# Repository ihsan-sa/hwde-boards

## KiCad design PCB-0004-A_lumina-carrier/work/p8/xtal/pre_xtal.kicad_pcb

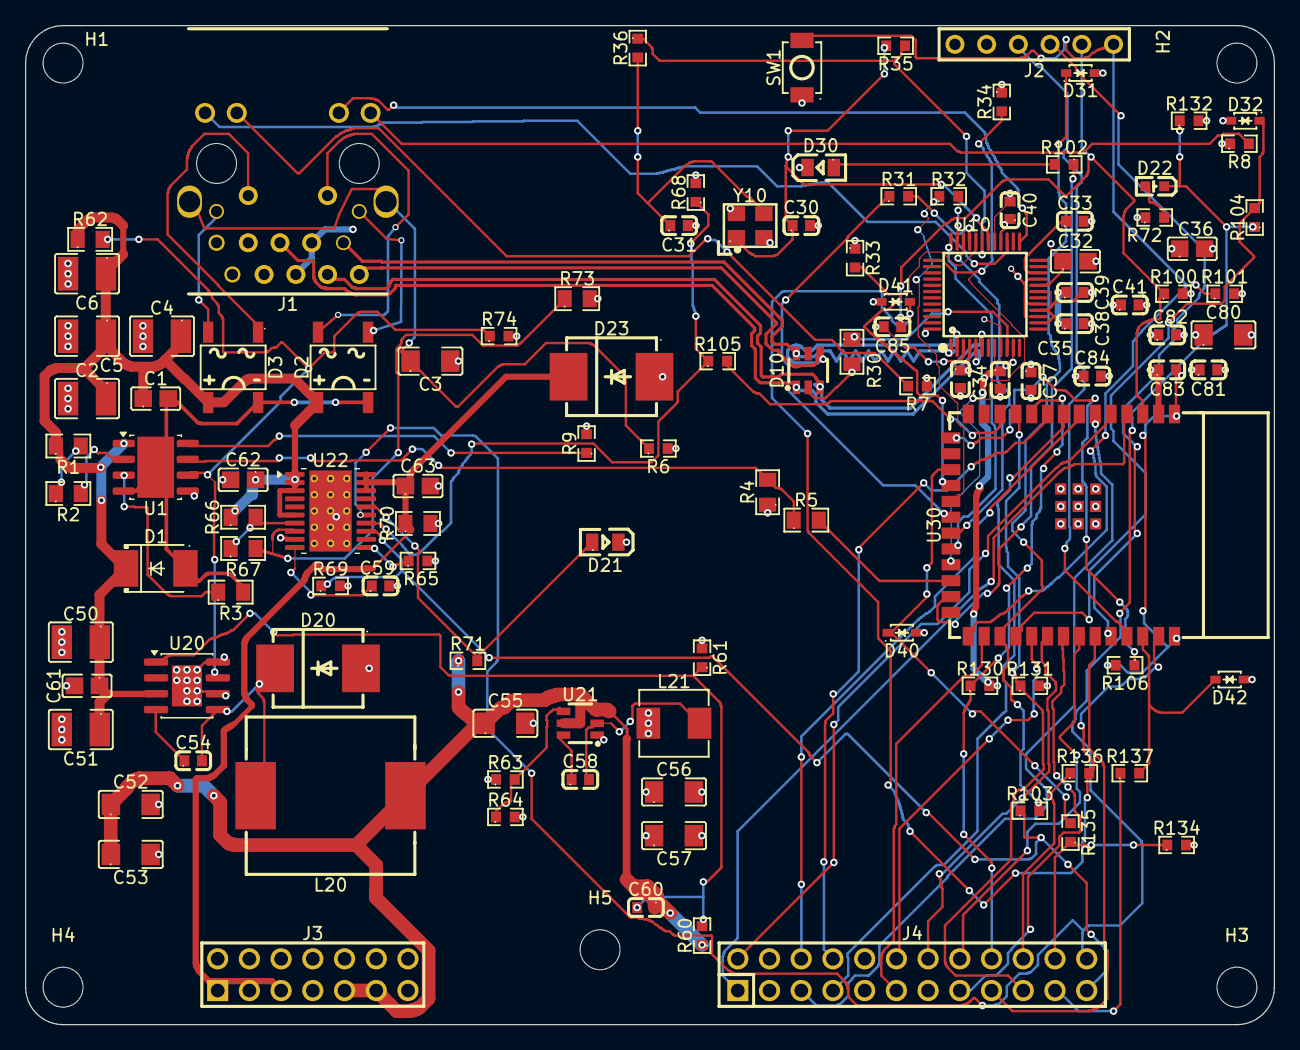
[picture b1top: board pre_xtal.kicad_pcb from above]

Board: 4 copper layers, 100.0 x 80.0 mm, 116 parts (0 on the bottom side), 85 nets.

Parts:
C1, C61, C62, C63: 100nF 100V X7R 0805; C0805
C2, C4, C5, C6: 10uF 100V X7R 1210; C1210
C3: 1nF 2kV X7R 1206; C1206
C30, C31: 27pF 50V NP0 0603; C0603
C32, C36: 4.7uF 25V X5R 0805; C0805
C33, C59: 10nF 50V X7R 0603; C0603
C34, C35, C37, C38, C39, C40, C41, C54, C58: 100nF 50V X7R 0603; C0603
C50, C51: 2.2uF 100V X7R 1210; C1210
C52, C53, C55, C56, C57: 22uF 25V X5R 1206; C1206
C60: 150pF 50V NP0 0603; C0603
C80: 22uF 25V X5R; C1206
C81, C82, C83: 100nF 50V X7R; C0603
C84, C85: 1uF 50V X5R; C0603
D1: SMBJ58A 58V 600W TVS; SMB_L4.3-W3.6-LS5.4-R-RD
D2: ABS210 2A 1000V bridge (Alt A); ABF_L5.1-W4.4-P4.00-LS6.2-BL
D3: ABS210 2A 1000V bridge (Alt B); ABF_L5.1-W4.4-P4.00-LS6.2-BL
D10: TPD4E1U06 4ch 0.55pF ESD array; SOT-23-6_L2.9-W1.6-P0.95-LS2.8-BR
D20, D23: SS510C 100V 5A Schottky SMC; SMC_L7.1-W6.2-LS8.1-R-RD
D21, D30: Green LED 0805; LED0805-R-RD
D22: Red LED 0603; LED-SMD_L1.6-W0.8-R-RD
D31, D32, D40, D41, D42: PESD3V3L1BA 3.3V ESD clamp SOD-323; SOD-323_L1.7-W1.3-LS2.6-BI
H1, H2, H3, H4, H5: MountingHole_3.2mm_M3
J1: LPJG0926HENL PoE+ RJ45 magjack; RJ45-TH_LPJG0926HENL_C22457393
J2: 1x6 2.54mm header (recovery); CONN-TH_DS1021-1X6SF11-B
J3: DS1021-2x7SF11-B 2x7 male header; HDR-TH_14P-P2.54-V-M-R2-C7-S2.54-1
J4: DS1021-2x12SF11-B 2x12 male header; HDR-TH_24P-P2.54-V-M-R2-C12-S2.54
L20: 68uH 3A 140mohm inductor; IND-SMD_L12.6-W13.5
L21: 4.7uH 4A 46mohm inductor; IND-SMD_L5.4-W5.2
R1, R2: 12.1k 1% 0805; R0805
R3: 90.9R 1% 0805; R0805
R4, R5: 10k 1% 0805; R0805
R6, R35: 1M 1% 0603; R0603
R7, R8, R72: 330R 1% 0603; R0603
R9, R36: 0R jumper 0603; R0603
R30: 12.4k 1% 0805; R0805
R31, R32: 22R 1% 0603; R0603
R33, R34, R64, R69, R71, R106, R132, R134: 10k 1% 0603; R0603
R60: 270k 1% 0603; R0603
R61, R68: 30k 1% 0603; R0603
R62, R70: 100k 1% 0805; R0805
R63: 33k 1% 0603; R0603
R65: 18k 1% 0603; R0603
R66: 620k 0.1% 0805; R0805
R67: 10k 0.1% 0805; R0805
R73: 12k 0.1% 0805; R0805
R74, R130, R131: 4.7k 1% 0603; R0603
R100, R101: 10k; R0603
R102: 330R; R0603
R103, R104, R105, R135, R136, R137: 1k 1% 0603; R0603
SW1: SMD tactile switch; SW-SMD_L3.9-W3.0-P4.45
U1: TPS2378DDAR; SOIC-8-1EP_3.9x4.9mm_P1.27mm_EP2.95x4.9mm_Mask2.71x3.4mm
U10: W5500; LQFP-48_L7.0-W7.0-P0.50-LS9.0-BL
U20: SCT2A25STER; SOIC-8-1EP_3.9x4.9mm_P1.27mm_EP2.41x3.3mm
U21: TPS563201DDCR; SOT-23-6_L2.9-W1.6-P0.95-LS2.8-BR
U22: TPS16630PWPR; HTSSOP-20-1EP_4.4x6.5mm_P0.65mm_EP3.4x6.5mm_Mask2.96x2.96mm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
U30: ESP32-S3-WROOM-1-N8; WIFIM-SMD_ESP32-S3-WROOM-1-N8
Y10: 25MHz 18pF CL crystal; OSC-SMD_4P-L3.2-W2.5-BL_SIT8008BI

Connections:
+3V3: C34.1, C35.1, C36.1, C37.1, C38.1, C39.1, C40.1, C41.1, C56.1, C57.1, C80.1, C81.1, C82.1, C83.1, C84.1, J1.4, J1.5, J2.2, J3.12, J3.14, L21.2, R4.1, R7.1, R8.1, R33.1, R34.1, R63.1, R72.1, R100.2, R101.2, R130.2, R131.2, R132.2, R134.2, U10.4, U10.8, U10.11, U10.15, U10.17, U10.21, U10.28, U30.2
+12V: C52.1, C53.1, C55.1, C60.1, J3.9, J3.11, L20.2, R60.1, R71.1, U21.3, U21.5
+48V_SW: C63.1, D23.2, J3.1, J3.3, J3.5, R70.1, U22.18, U22.19, U22.20
/ADC0: D41.1, R136.2, U30.39
/ADC1: D42.1, R137.2, U30.38
/CDB: R62.2, R74.1, U1.6, U20.7
/DSPI_CSn: J4.17, U30.35
/DSPI_MISO: J4.16, U30.34
/DSPI_MOSI: J4.15, U30.33
/DSPI_SCK: J4.14, U30.32
/ENABLE: J4.23, R69.1, R103.1, U22.13
/ETH_CSn: R33.2, U10.32, U30.18
/ETH_INTn: U10.36, U30.22
/ETH_LED_ACT: J1.18, U10.27
/ETH_LED_LINK: J1.16, U10.25
/ETH_MISO: U10.34, U30.21
/ETH_MOSI: R32.1, U30.19
/ETH_RSTn: R34.2, U10.37, U30.23
/ETH_RXN: D10.1, J1.6, U10.5
/ETH_RXP: D10.3, J1.3, U10.6
/ETH_SCLK: R31.1, U30.20
/ETH_TXN: D10.6, J1.2, U10.1
/ETH_TXP: D10.4, J1.1, U10.2
/FAULT: D22.2, J4.24, R104.1, R132.1, U22.15
/I2C_SCL: J4.18, R130.1, U30.10
/I2C_SDA: J4.19, R131.1, U30.11
/ID_ADC: D40.1, R135.2, U30.17
/IMON: R68.1, R105.1, U22.14
/PWM0: J4.1, U30.4
/PWM1: J4.2, U30.5
/PWM2: J4.5, U30.6
/PWM3: J4.6, U30.7
/PWM4: J4.7, U30.8
/PWM5: J4.8, U30.9
/PWM6: J4.11, U30.28
/PWM7: J4.12, U30.31
/T2P: R5.2, U30.24
/eth/1V2O: C33.1, U10.22
/eth/EXRES: R30.1, U10.10
/eth/MOSI_PHY: R32.2, U10.35
/eth/SCLK_PHY: R31.2, U10.33
/eth/TOCAP: C32.1, U10.20
/eth/XI: C30.1, R35.1, U10.30, Y10.1
/eth/XO: R35.2, R36.1, U10.31
/eth/XO_XTAL: C31.1, R36.2, Y10.3
/expansion/ADC0_CONN: J4.20, R136.1
/expansion/ADC1_CONN: J4.21, R137.1
/expansion/ID_ADC_CONN: J4.22, R134.1, R135.1
/mcu/BOOT: J2.6, R101.1, SW1.1, U30.27
/mcu/EN: C85.1, J2.5, R100.1, U30.3
/mcu/ENABLE_M: D31.1, R103.2, U30.29
/mcu/FAULT_M: D32.1, R104.2, U30.30
/mcu/IMON_M: R105.2, U30.12
/mcu/IO3_STRAP: R106.1, U30.15
/mcu/RXD0: J2.4, U30.36
/mcu/STATUS: R102.1, U30.25
/mcu/STATUS_A: D30.1, R102.2
/mcu/TXD0: J2.3, U30.37
/poe/APD: R9.1, U1.8
/poe/CLS: R3.1, U1.3
/poe/DEN: R2.2, U1.2
/poe/DEN_TAP: R1.2, R2.1
/poe/LED_G_A: J1.15, R8.2
/poe/LED_Y_A: J1.17, R7.2
/poe/POE_TAP_A1: D2.1, J1.11
/poe/POE_TAP_A2: D2.2, J1.12
/poe/POE_TAP_B1: D3.1, J1.13
/poe/POE_TAP_B2: D3.2, J1.14
/poe/SHIELD: C3.1, J1.19, J1.20, R6.1
/poe/T2P_OD: R4.2, R5.1, U1.7
/pwr/BST: C54.1, U20.4
/pwr/BST33: C58.1, U21.6
/pwr/DVDT: C59.1, U22.10
/pwr/FB33: R63.2, R64.1, U21.4
/pwr/FB48: C60.2, R60.2, R61.1, U20.1
/pwr/FLT_LED: D22.1, R72.2
/pwr/ILIM: R65.1, U22.11
/pwr/OVP: R67.2, R73.1, U22.8
/pwr/PGOOD: D21.1, R71.2, U22.16
/pwr/SW: C54.2, D20.2, L20.1, U20.5
/pwr/SW33: C58.2, L21.1, U21.2
/pwr/UVLO: R66.2, R67.1, U22.7
GND: C2.2, C3.2, C4.2, C5.2, C6.2, C30.2, C31.2, C32.2, C33.2, C34.2, C35.2, C36.2, C37.2, C38.2, C39.2, C40.2, C41.2, C50.2, C51.2, C52.2, C53.2, C55.2, C56.2, C57.2, C59.2, C61.2, C62.2, C63.2, C80.2, C81.2, C82.2, C83.2, C84.2, C85.2, D10.2, D20.1, D21.2, D23.1, D30.2, D31.2, D32.2, D40.2, D41.2, D42.2, J2.1, J3.2, J3.4, J3.6, J3.7, J3.8, J3.10, J3.13, J4.3, J4.4, J4.9, J4.10, J4.13, R6.2, R9.2, R30.2, R61.2, R64.2, R65.2, R68.2, R69.2, R70.2, R73.2, R74.2, R106.2, SW1.2, U1.5, U10.3, U10.9, U10.14, U10.16, U10.19, U10.23, U10.29, U10.48, U20.6, U20.8, U20.9, U21.1, U22.9, U22.21, U30.1, U30.40, U30.41, Y10.2, Y10.4
V48_RAW: C1.1, C2.1, C4.1, C5.1, C6.1, C50.1, C51.1, C61.1, C62.1, D1.2, D2.3, D3.3, R1.1, R62.1, R66.1, U1.1, U20.3, U22.1, U22.2, U22.3, U22.6
V48_RTN: C1.2, D1.1, D2.4, D3.4, R3.2, U1.4, U1.9

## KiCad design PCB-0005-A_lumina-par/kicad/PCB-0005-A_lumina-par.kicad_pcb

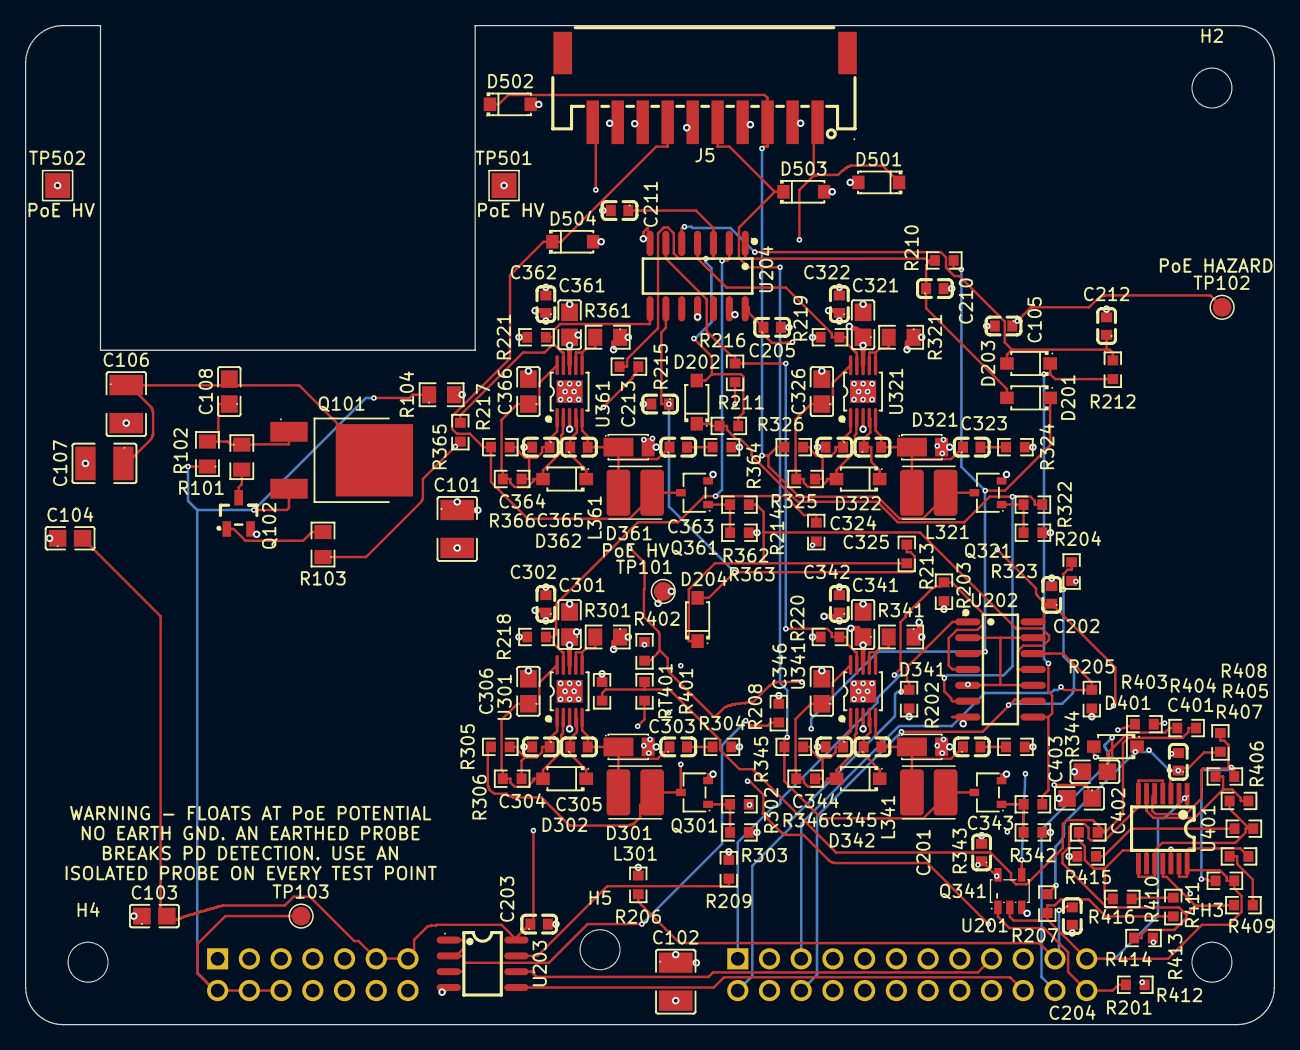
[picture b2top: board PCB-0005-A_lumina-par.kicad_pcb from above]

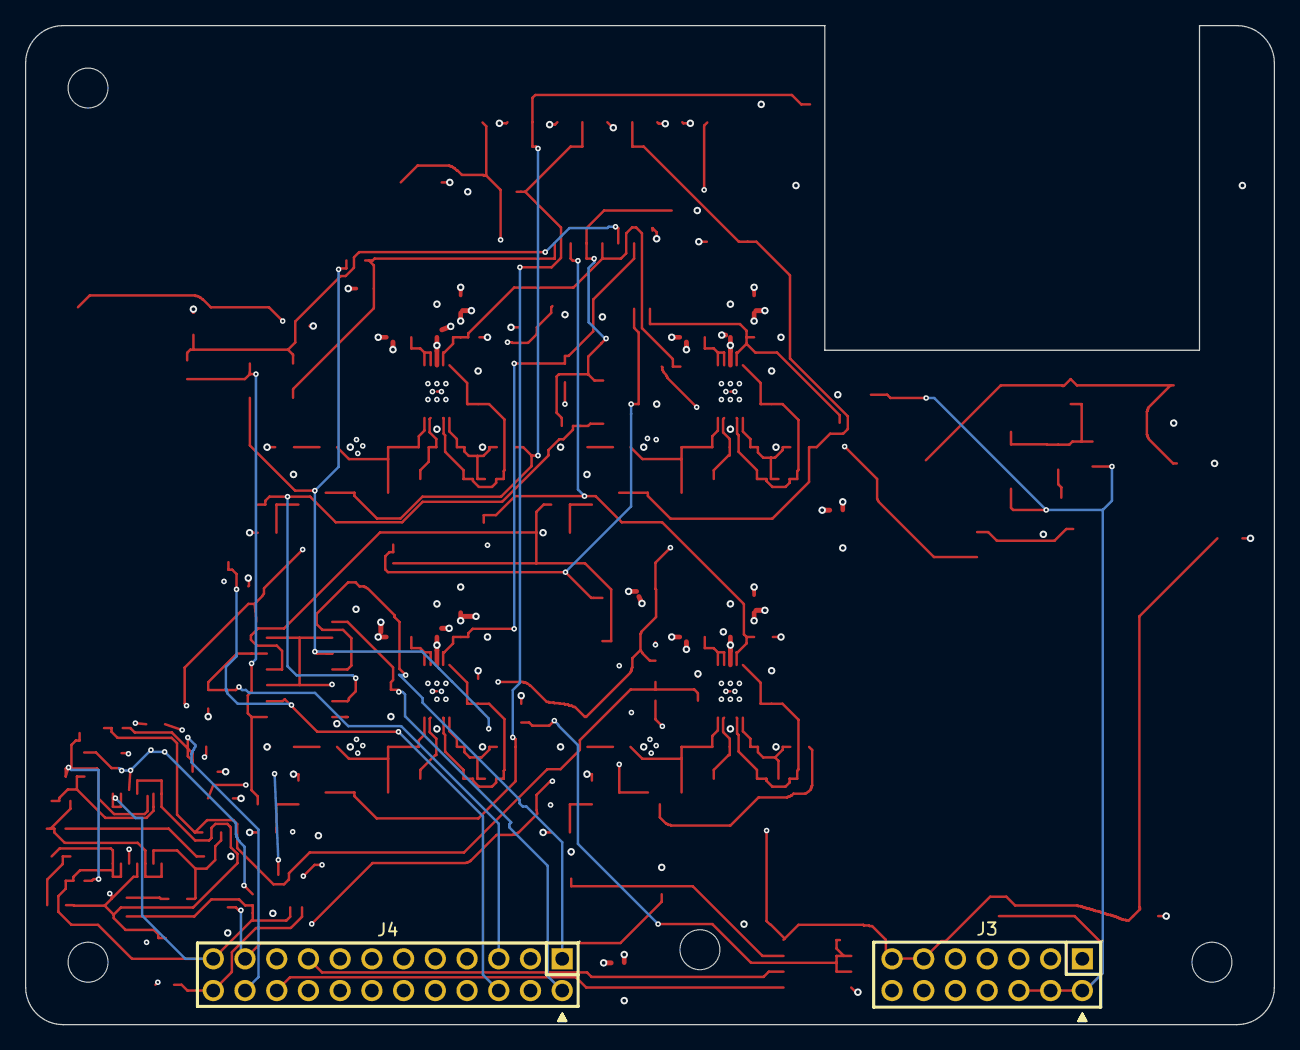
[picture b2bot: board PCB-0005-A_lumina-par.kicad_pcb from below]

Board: 4 copper layers, 100.0 x 80.0 mm, 158 parts (2 on the bottom side), 76 nets.

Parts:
C101, C102: 22uF 25V X7R 1210; C1210
C103, C104: 10uF 16V X7R 0805; C0805
C105, C201, C202, C203, C204, C205, C302, C305, C322, C325, C342, C345, C362, C365, C401: 100nF 50V X7R 0603; C0603
C106, C107: 10uF 100V X7R 1210; C1210
C108: 33nF 100V X7R 0805; C0805
C210, C211, C212, C213: 10nF 50V X7R 0603; C0603
C301, C306, C321, C326, C341, C346, C361, C366, C402, C403: 4.7uF 25V X7R 0805; C0805
C303, C323, C343, C363: 1nF 100V X7R 0603; C0603
C304, C324, C344, C364: 470pF 50V C0G 0603; C0603
D201, D202, D203, D204, D401: 1N4148W switching diode, SOD-123; SOD-123F_L2.7-W1.6-LS3.8-RD
D301, D321, D341, D361: DFLS160-7 60V 1A Schottky; POWERDI-123_L2.8-W1.8-LS3.7-RD
D302, D322, D342, D362: 1N4148W 100V fast switching; SOD-123F_L2.7-W1.6-LS3.8-RD
D501, D502, D503, D504: SMF15A 15V unidirectional TVS, SOD-123; SOD-123_L2.7-W1.8-LS3.7-RD
H2, H3, H4, H5: MountingHole_3.2mm_M3
J3: DS1023-2*7SF11 2x7 socket 2.54mm 600V; HDR-TH_14P-P2.54-V-F-R2-C7-S2.54-1
J4: DS1023-2*12SF11 2x12 socket, 2.54 mm, 600 V, 3 A/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; HDR-TH_24P-P2.54-V-F-R2-C12-S2.54
J5: S10B-PH-SM4-TB JST PH 10-way SMD header, 2.0 mm; CONN-SMD_S10B-PH-SM4-TB-LF-SN
L301, L321, L341, L361: 47uH shielded 950mA; L_Cenker_CKCS4030
Q101: NCE01P13K -100V P-MOSFET TO-252; TO-252-2_L6.6-W6.1-P4.57-LS10.1-TL-CW
Q102: BSS123 100V N-MOSFET SOT-23; SOT-23-3_L2.9-W1.5-P1.90-LS2.6-BR
Q301, Q321, Q341, Q361: SSM3K2615R 60V 2A N-FET; SOT-23F_L2.9-W1.8-P1.90-LS2.4-BR
R101, R104: 100k 0805 1%; R0805
R102, R103: 10k 0805 1%; R0805
R201, R202, R203, R204, R205, R207, R210, R211, R212, R213, R409, R411, R412, R414: 100k 0603 1%; R0603
R206: 4.7k 0603 1%; R0603
R208, R214, R215, R216, R217: 0R 0603; R0603
R209, R218, R219, R220, R221, R401, R403, R410, R413, R415: 10k 0603 1%; R0603
R301, R321, R341, R361: 0.75R 1% 0805; R0805
R302, R322, R342, R362: 150R 1% 0603; R0603
R303, R323, R343, R363: 100k 1% 0603; R0603
R304, R324, R344, R364: 10R 0603; R0603
R305, R325, R345, R365: 10k 1% 0603; R0603
R306, R326, R346, R366: 30k 1% 0603; R0603
R402, R404: 150R 0603 1%; R0603
R405: 2.7k 0603 1%; R0603
R406: 27k 0603 1%; R0603
R407: 1.2k 0603 1%; R0603
R408, R416: 1.6k 0603 1%; R0603
RT401: 10k B3950 +-1% NTC 0603; R0603
TP101, TP102, TP103: TestPoint; TestPoint_Pad_D1.5mm
TP501, TP502: thermocouple pad, bare Cu; TestPoint_Pad_2.0x2.0mm
U201: SN74LVC1G08DBVR single 2-input AND, SOT-23-5; SOT-23-5_L3.0-W1.7-P0.95-LS2.8-BR
U202: SN74LVC00ADR quad 2-input NAND, SOIC-14; SOIC-14_L8.7-W3.9-P1.27-LS6.0-BL
U203: M24C32-WMN6TP 32 kbit I2C EEPROM, SOIC-8; SOIC-8_L5.0-W4.0-P1.27-LS6.0-BL
U204: SN74LVC14ADR hex Schmitt-trigger inverter, SOIC-14; SOIC-14_L8.7-W3.9-P1.27-LS6.0-BL
U301, U321, U341, U361: TPS92515HVDGQR; MSOP-10_L3.0-W3.0-P0.50-LS5.0-BL-EP
U401: LM339LVPWR quad open-drain comparator TSSOP-14; TSSOP-14_L5.0-W4.4-P0.65-LS6.4-BL

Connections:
+3V3: C103.2, C104.2, C105.1, C201.1, C202.1, C203.1, C205.1, C401.1, D401.1, J3.11, J3.13, R207.2, R401.1, R403.1, R405.1, TP102.1, U201.5, U202.14, U203.8, U204.14, U401.3
+12V: C101.1, C102.1, C301.1, C302.1, C321.1, C322.1, C341.1, C342.1, C361.1, C362.1, J3.10, J3.12, R301.1, R321.1, R341.1, R361.1, TP101.1, U301.8, U321.8, U341.8, U361.8
+48V_SW: J3.2, J3.4, J3.6, Q101.3, R101.1, R104.1, TP103.1
/ADC0: C402.1, J4.19, R402.2
/ADC1: C403.1, J4.22, R404.2
/DRV_EN0: R214.2, R218.1, U204.2, U301.9
/DRV_EN1: R215.2, R219.1, U204.4, U321.9
/DRV_EN2: R216.2, R220.1, U204.6, U341.9
/DRV_EN3: R217.2, R221.1, U204.8, U361.9
/EN_OK: R103.1, R214.1, R215.1, R216.1, R217.1, U201.4, U202.2, U202.5, U202.10, U202.13
/FAULT: J4.23, R207.1, R409.1, R410.1, R412.1, U201.2, U401.1, U401.2, U401.13, U401.14
/LED0_A: D501.1, J5.1, L301.2, Q301.3, R305.1
/LED1_A: D502.1, J5.3, L321.2, Q321.3, R325.1
/LED2_A: D503.1, J5.5, L341.2, Q341.3, R345.1
/LED3_A: D504.1, J5.7, L361.2, Q361.3, R365.1
/NTC_LED: J5.10, R402.1, R403.2, R413.1
/SHUNT0: D201.1, R210.1, R302.1, U202.3
/SHUNT1: D202.1, R211.1, R322.1, U202.6
/SHUNT2: D203.1, R212.1, R342.1, U202.8
/SHUNT3: D204.1, R213.1, R362.1, U202.11
/control/EE_ADDR: R208.1, U203.1, U203.2, U203.3
/control/EE_WC: R209.1, U203.7
/control/ENABLE: J4.24, R201.1, U201.1
/control/I2C_SCL: J4.17, U203.6
/control/I2C_SDA: J4.20, U203.5
/control/IDLE0: C210.1, D201.2, R210.2, U204.1
/control/IDLE1: C211.1, D202.2, R211.2, U204.3
/control/IDLE2: C212.1, D203.2, R212.2, U204.5
/control/IDLE3: C213.1, D204.2, R213.2, U204.9
/control/ID_ADC: C204.1, J4.21, R206.1
/control/PWM0: J4.2, R202.1, U202.1
/control/PWM1: J4.1, R203.1, U202.4
/control/PWM2: J4.6, R204.1, U202.9
/control/PWM3: J4.5, R205.1, U202.12
/drivers/BOOT0: C305.1, D302.1, U301.4
/drivers/BOOT1: C325.1, D322.1, U321.4
/drivers/BOOT2: C345.1, D342.1, U341.4
/drivers/BOOT3: C365.1, D362.1, U361.4
/drivers/COFF0: C304.1, R305.2, R306.2, U301.1
/drivers/COFF1: C324.1, R325.2, R326.2, U321.1
/drivers/COFF2: C344.1, R345.2, R346.2, U341.1
/drivers/COFF3: C364.1, R365.2, R366.2, U361.1
/drivers/CSN0: R301.2, U301.6, U301.7
/drivers/CSN1: R321.2, U321.6, U321.7
/drivers/CSN2: R341.2, U341.6, U341.7
/drivers/CSN3: R361.2, U361.6, U361.7
/drivers/SHG0: Q301.1, R302.2, R303.1
/drivers/SHG1: Q321.1, R322.2, R323.1
/drivers/SHG2: Q341.1, R342.2, R343.1
/drivers/SHG3: Q361.1, R362.2, R363.1
/drivers/SNUB0: C303.2, R304.1
/drivers/SNUB1: C323.2, R324.1
/drivers/SNUB2: C343.2, R344.1
/drivers/SNUB3: C363.2, R364.1
/drivers/SW0: C303.1, C305.2, D301.1, L301.1, U301.5
/drivers/SW1: C323.1, C325.2, D321.1, L321.1, U321.5
/drivers/SW2: C343.1, C345.2, D341.1, L341.1, U341.5
/drivers/SW3: C363.1, C365.2, D361.1, L361.1, U361.5
/drivers/VCC0: C306.1, D302.2, R306.1, U301.2, U301.10
/drivers/VCC1: C326.1, D322.2, R326.1, U321.2, U321.10
/drivers/VCC2: C346.1, D342.2, R346.1, U341.2, U341.10
/drivers/VCC3: C366.1, D362.2, R366.1, U361.2, U361.10
/power/Q101_G: C108.1, Q101.1, R101.2, R102.1
/power/Q102_D: Q102.3, R102.2
/power/Q102_G: Q102.1, R103.2
/power/V48_B: C106.1, C107.1, C108.2, Q101.2
/thermal/CMP_BRD: R414.2, R415.2, U401.9
/thermal/CMP_LED: D401.2, R411.2, R413.2, U401.4, U401.7, U401.11
/thermal/HYS_BRD: R412.2, R414.1
/thermal/HYS_LED: R409.2, R411.1
/thermal/LAD_D: R408.2, R416.1
/thermal/NTC_BRD: R401.2, R404.1, R415.1, RT401.1
/thermal/VREF_EHOT: R406.2, R407.1, U401.6
/thermal/VREF_HOT2: R407.2, R408.1, U401.8, U401.10
/thermal/VREF_OPEN: R405.2, R406.1, R410.2, U401.5
GND: C101.2, C102.2, C103.1, C104.1, C105.2, C106.2, C107.2, C201.2, C202.2, C203.2, C204.2, C205.2, C210.2, C211.2, C212.2, C213.2, C301.2, C302.2, C304.2, C306.2, C321.2, C322.2, C324.2, C326.2, C341.2, C342.2, C344.2, C346.2, C361.2, C362.2, C364.2, C366.2, C401.2, C402.2, C403.2, D301.2, D321.2, D341.2, D361.2, D501.2, D502.2, D503.2, D504.2, J3.1, J3.3, J3.5, J3.7, J3.8, J3.9, J3.14, J4.3, J4.4, J4.9, J4.10, J4.14, J5.2, J5.4, J5.6, J5.8, J5.9, Q102.2, Q301.2, Q321.2, Q341.2, Q361.2, R104.2, R201.2, R202.2, R203.2, R204.2, R205.2, R206.2, R208.2, R209.2, R218.2, R219.2, R220.2, R221.2, R303.2, R304.2, R323.2, R324.2, R343.2, R344.2, R363.2, R364.2, R416.2, RT401.2, TP501.1, TP502.1, U201.3, U202.7, U203.4, U204.7, U204.11, U204.13, U301.3, U301.11, U321.3, U321.11, U341.3, U341.11, U361.3, U361.11, U401.12

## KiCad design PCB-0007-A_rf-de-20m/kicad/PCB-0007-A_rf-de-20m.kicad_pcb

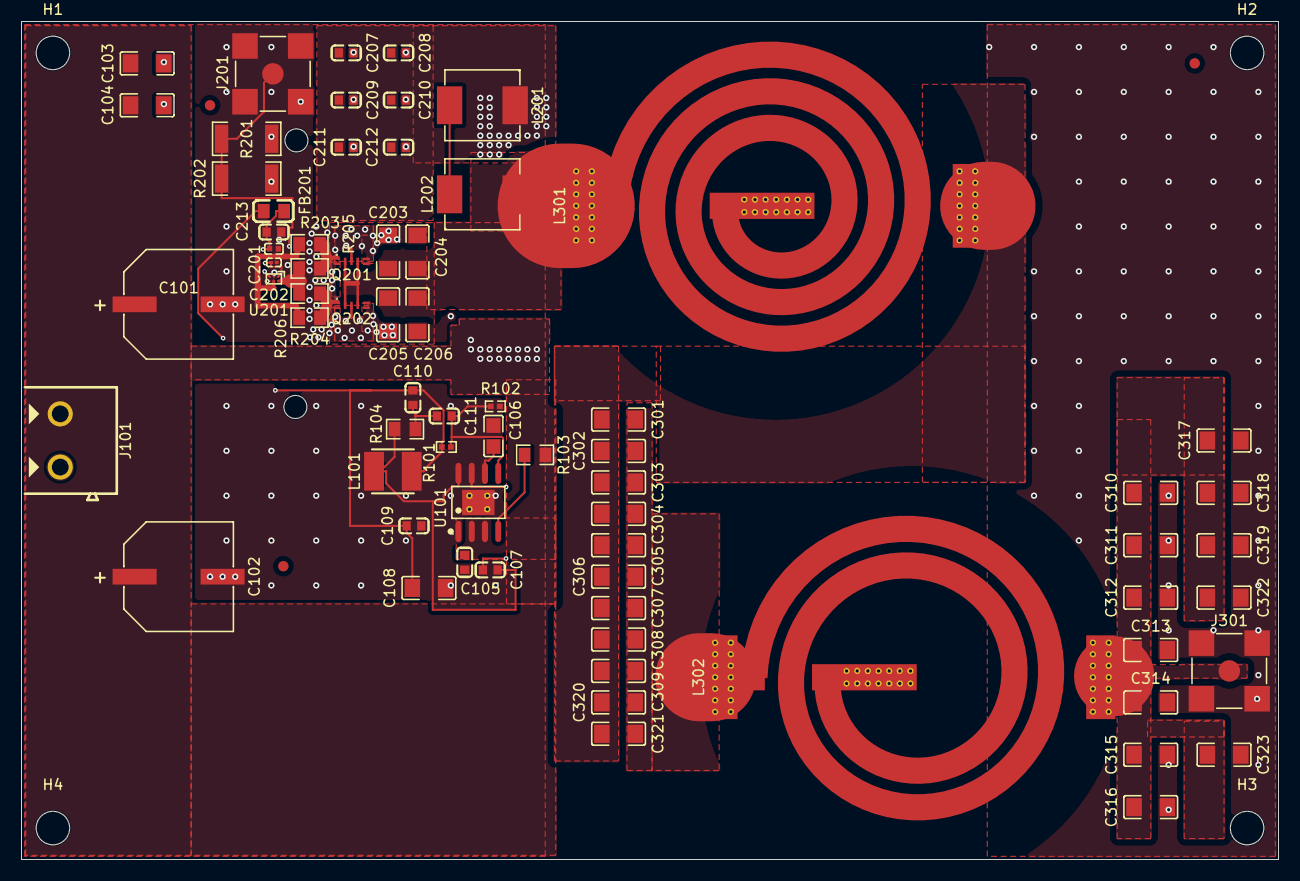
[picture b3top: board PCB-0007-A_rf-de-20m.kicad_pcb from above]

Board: 4 copper layers, 120.0 x 80.0 mm, 80 parts (0 on the bottom side), 20 nets.

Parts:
C101, C102: 100uF 63V alu electrolytic; CAP-SMD_BD10.0-L10.3-W10.3-LS11.0-FD_1
C103, C104: 2.2uF 100V X7R 1206; C1206
C105, C109, C111: 100nF 100V X7R 0603; C0603
C106: 2.2uF 50V X7R 0805; C0805
C107, C207, C208, C209, C210: 10nF 100V X7R 0603; C0603
C108: 22uF 16V X7R 1206; C1206
C110, C211, C212: 1nF 100V C0G 0603; C0603
C201: 100nF 16V X7R 0402; C0402
C202: 10nF 25V X7R 0201; C0201
C203, C205, C206, C301, C302, C303, C304, C305, C306, C307, C308, C309, C310, C311, C312, C313, C314, C315, C316, C317, C318: 56pF 1kV C0G 1206; C1206
C204, C319, C320, C321, C322, C323: 27pF 1kV C0G 1206; C1206
C213: 1uF 16V X7R 0603; C0603
FB201: 120R@100MHz bead 3A 30mohm; L0805
FID1, FID2, FID3: Fiducial_1mm_Mask2mm
H1, H2, H3, H4: MountingHole_3.2mm_M3
H5, H6: MountingHole_2.2mm_M2_ISO7380
HS1: HEATSINK_LAND; HS2_HEATSINK_LAND
J101: KF128-5.08-2P 2pos 5.08mm 24A/250V; CONN-TH_P5.08_KF128-5.08-2P_EDGETRIM
J201, J301: SMA jack 50R SMD (CONSMA001); SMA-SMD_CONSMA001-SMD-G-T
L101: 22uH 1A shielded; IND-SMD_L4.0-W4.0_SLW4010S
L201, L202: 470nH 20A 4.1mohm; IND-SMD_L7.0-W6.6_FXL0630
L301: 164nH; SPIRAL_L164N
L302: 110nH; SPIRAL_L110N
Q201, Q202: EPC2019 200V eGaN; TRS-SMD_EPC2019
R101: 30.9k 0402 1%; R0402
R102: 10.0k 0402 1%; R0402
R103, R104: 100k 0805 1% 150V; R0805
R201, R202: 100R 2010 1% 750mW; R2010
R203, R204, R205, R206: 4R7 0805 1% 250mW; R0805
U101: LM5017 100V sync COT buck; SOIC-8-EP_LM5017_TI-MRA08B
U201: LMG1020 5V GaN driver 7A/5A; BGA-6_L1.3-W0.8-P0.40-TL_PTMAG3001A2YBGR

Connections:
+5V: C108.1, C109.1, C110.2, FB201.1, L101.2, R101.1
+5V_DRV: C201.1, C202.1, C213.1, FB201.2, U201.A1
+40V: C101.1, C102.1, C103.1, C104.1, C105.1, C207.1, C208.1, C209.1, C210.1, C211.1, C212.1, J101.1, L201.1, R103.2, U101.2, U101.3
/SW: C203.1, C204.1, C205.1, C206.1, L202.2, L301.1, Q201.3, Q201.5, Q202.3, Q202.5
/hk/BST: C107.1, U101.7
/hk/BUCK_SW: C107.2, L101.1, R104.1, U101.8
/hk/FB: C111.2, R101.2, R102.1, U101.5
/hk/RINJ: C110.1, C111.1, R104.2
/hk/RON: R103.1, U101.4
/hk/VCC: C106.1, U101.6
/stage/DRIVE: J201.5, R201.1, R202.1, U201.C1
/stage/GATE_OFF: R205.1, R206.1, U201.B2
/stage/GATE_ON: R203.1, R204.1, U201.A2
/stage/GATE_Q1: Q201.1, R203.2, R205.2
/stage/GATE_Q2: Q202.1, R204.2, R206.2
/stage/L201_MID: L201.2, L202.1
/tank/RFOUT: C310.1, C311.1, C312.1, C313.1, C314.1, C315.1, C316.1, C317.1, C318.1, C319.1, C322.1, C323.1, J301.5, L302.2
/tank/TANK_A: C301.1, C302.1, C303.1, C304.1, C305.1, C306.1, C307.1, C308.1, C309.1, C320.1, C321.1, L301.2
/tank/TANK_B: C301.2, C302.2, C303.2, C304.2, C305.2, C306.2, C307.2, C308.2, C309.2, C320.2, C321.2, L302.1
GND: C101.2, C102.2, C103.2, C104.2, C105.2, C106.2, C108.2, C109.2, C201.2, C202.2, C203.2, C204.2, C205.2, C206.2, C207.2, C208.2, C209.2, C210.2, C211.2, C212.2, C213.2, C310.2, C311.2, C312.2, C313.2, C314.2, C315.2, C316.2, C317.2, C318.2, C319.2, C322.2, C323.2, HS1.1, J101.2, J201.1, J201.2, J201.3, J201.4, J301.1, J301.2, J301.3, J301.4, Q201.2, Q201.4, Q201.6, Q201.7, Q202.2, Q202.4, Q202.6, Q202.7, R102.2, R201.2, R202.2, U101.1, U101.9, U201.B1, U201.C2

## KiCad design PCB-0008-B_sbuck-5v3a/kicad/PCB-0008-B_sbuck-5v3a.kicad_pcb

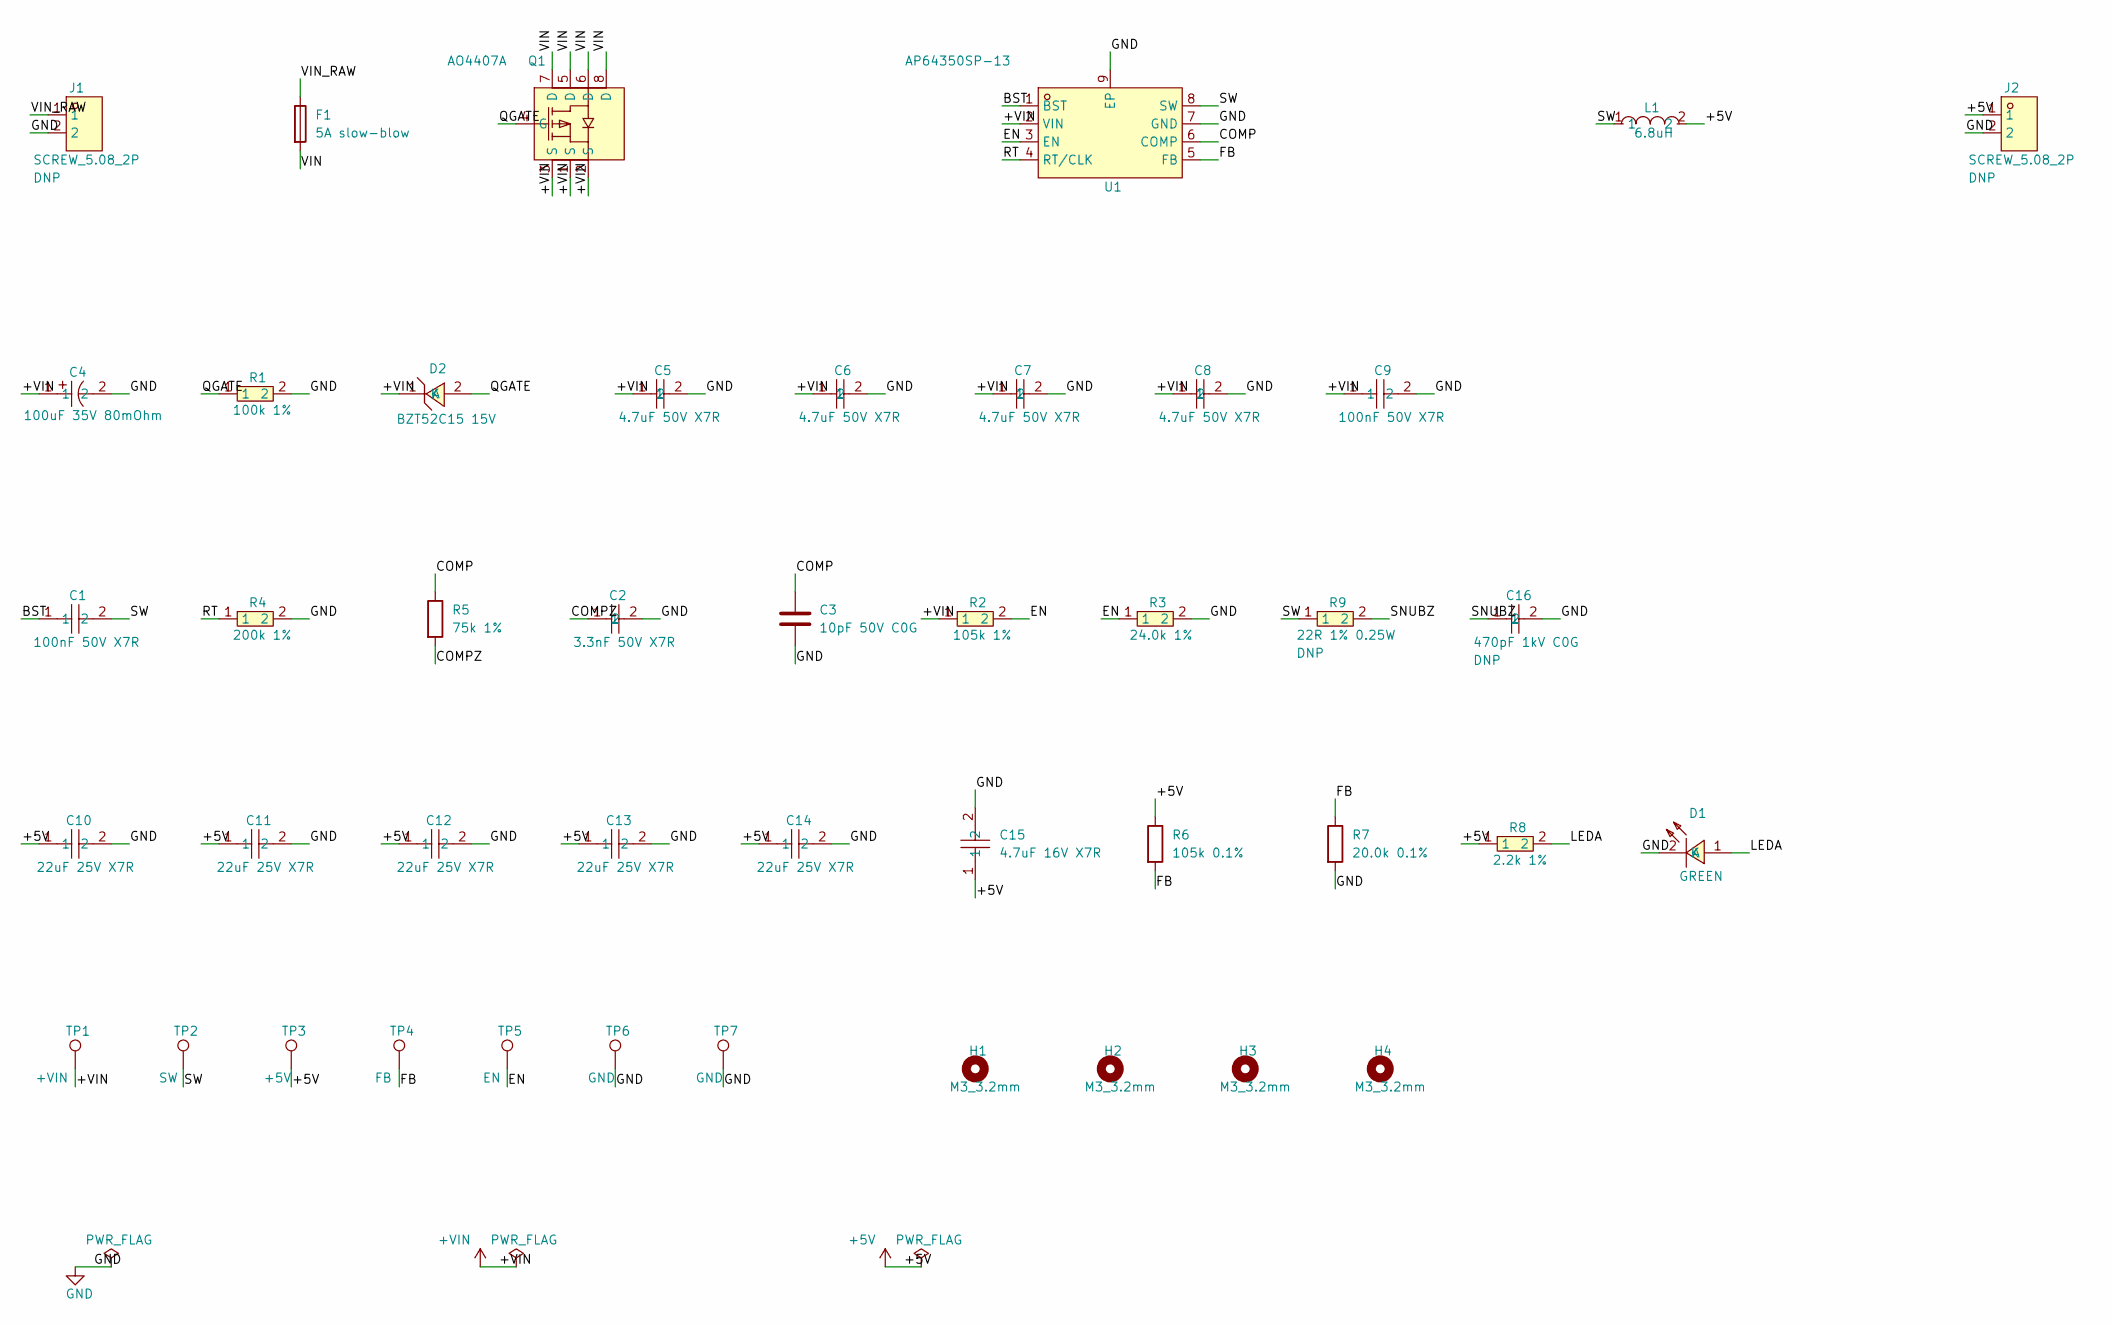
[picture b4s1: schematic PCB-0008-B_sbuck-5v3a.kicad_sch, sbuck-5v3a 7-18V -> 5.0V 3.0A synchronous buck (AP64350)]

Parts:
C1, C9: 100nF 50V X7R; C0603; LCSC C14663
C2: 3.3nF 50V X7R; C0603; LCSC C1613
C3: 10pF 50V C0G; C0603; LCSC C106245
C4: 100uF 35V 80mOhm; CAP-SMD_BD6.3-L6.5-W6.5-LS7.2-FD; LCSC C2982822
C5, C6, C7, C8: 4.7uF 50V X7R; C1206; LCSC C29823
C10, C11, C12, C13, C14: 22uF 25V X7R; C1210; LCSC C49118556
C15: 4.7uF 16V X7R; C0805; LCSC C277499
C16: 470pF 1kV C0G; C1206; LCSC C107177
D1: GREEN; LED0805-R-RD; LCSC C2297
D2: BZT52C15 15V; SOD-123_L2.7-W1.6-LS3.7-RD; LCSC C173427
F1: 5A slow-blow; Fuse_1206_C1T_BelVendorLand; LCSC C3163312
H1, H2, H3, H4: M3_3.2mm; MountingHole_3.2mm_M3
J1, J2: SCREW_5.08_2P; CONN-TH_2P-P5.08_DB128L-5.08-2P; LCSC C395868
L1: 6.8uH; IND-SMD_L11.5-W10.0; LCSC C5298292
Q1: AO4407A; SOIC-8_L4.9-W3.9-P1.27-LS6.0-BL; LCSC C16072
R1: 100k 1%; R0603; LCSC C25803
R2: 105k 1%; R0603; LCSC C16840
R3: 24.0k 1%; R0603; LCSC C23352
R4: 200k 1%; R0603; LCSC C25811
R5: 75k 1%; R0603; LCSC C23242
R6: 105k 0.1%; R0603; LCSC C491109
R7: 20.0k 0.1%; R0603; LCSC C723637
R8: 2.2k 1%; R0603; LCSC C4190
R9: 22R 1% 0.25W; R1206; LCSC C17958
TP1: +VIN; TestPoint_Pad_D1.5mm
TP2: SW; TestPoint_Pad_D1.5mm
TP3: +5V; TestPoint_Pad_D1.5mm
TP4: FB; TestPoint_Pad_D1.5mm
TP5: EN; TestPoint_Pad_D1.5mm
TP6, TP7: GND; TestPoint_Pad_D1.5mm
U1: AP64350SP-13; SO-8_L4.9-W3.9-P1.27-LS6.0-BL-EP; LCSC C2071691

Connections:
+5V: C10.1, C11.1, C12.1, C13.1, C14.1, C15.1, J2.1, L1.2, R6.1, R8.1, TP3.1
+VIN: C4.1, C5.1, C6.1, C7.1, C8.1, C9.1, D2.1 (K), Q1.1 (S), Q1.2 (S), Q1.3 (S), R2.1, TP1.1, U1.2 (VIN)
/BST: C1.1, U1.1 (BST)
/COMP: C3.1, R5.1, U1.6 (COMP)
/COMPZ: C2.1, R5.2
/EN: R2.2, R3.1, TP5.1, U1.3 (EN)
/FB: R6.2, R7.1, TP4.1, U1.5 (FB)
/LEDA: D1.1 (A), R8.2
/QGATE: D2.2 (A), Q1.4 (G), R1.1
/RT: R4.1, U1.4 (RT/CLK)
/SNUBZ: C16.1, R9.2
/SW: C1.2, L1.1, R9.1, TP2.1, U1.8 (SW)
/VIN: F1.2, Q1.5 (D), Q1.6 (D), Q1.7 (D), Q1.8 (D)
/VIN_RAW: F1.1, J1.1
GND: C2.2, C3.2, C4.2, C5.2, C6.2, C7.2, C8.2, C9.2, C10.2, C11.2, C12.2, C13.2, C14.2, C15.2, C16.2, D1.2 (K), J1.2, J2.2, R1.2, R3.2, R4.2, R7.2, TP6.1, TP7.1, U1.7 (GND), U1.9 (EP)

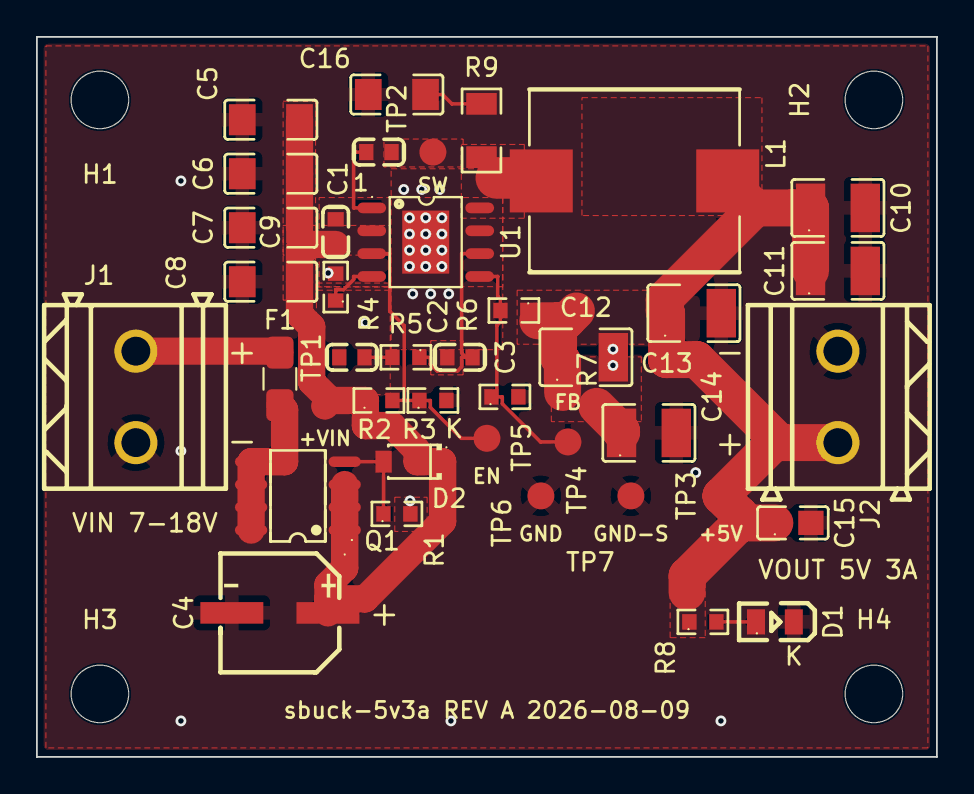
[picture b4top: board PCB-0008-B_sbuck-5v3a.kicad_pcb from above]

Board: 4 copper layers, 50.0 x 40.0 mm, 44 parts (0 on the bottom side), 15 nets.

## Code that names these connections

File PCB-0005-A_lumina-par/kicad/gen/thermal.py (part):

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
INPUT PROTECTION - SECTION D2.  THE E-2 FIX.  DO NOT REMOVE EITHER PART.
-------------------------------------------------------------------------
`/NTC_LED` arrives on J5 pin 10 from an off-board 10-way harness it shares
with four LED anodes that sit at up to 6.8 V in normal operation and reach
the SMF15A clamp region (VBR 16.7 V, VC 24.4 V at 8.2 A) whenever a string
opens.  U401's inputs are abs-max 6 V with no clamp to V+.  One crimp error
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the exact fault class this block exists to catch.  Two elements fix it and
neither works without the other:

  R413  10 k in series, NTC_LED -> CMP_LED (the three comparator pins).
  D401  1N4148W, anode CMP_LED, cathode +3V3 - the clamp the die does not
        have.  Silicon, NOT Schottky, on purpose: at 85 C a Schottky's
        reverse leakage would be tens of uA into a 10 k source impedance
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# ------------------------------------------------------------------- nets
# Sheet-LOCAL label spellings.  The four interface nets are exposed as
# hierarchical pins with these bare names; the ROOT sheet places the local
# label that turns them into the canonical "/FAULT", "/NTC_LED", "/ADC0",
# "/ADC1" of sheets.md s2 (a child-only label would yield "/thermal/NAME").
# NTC_BRD is sheet-internal by design (sheets.md s2) and therefore becomes
# "/thermal/NTC_BRD" - nothing in constraints.json or P5-P8 keys off it.
# +3V3 and GND are bare GLOBAL power symbols, never hierarchical pins.
N_FAULT = "FAULT"
N_NTC_LED = "NTC_LED"
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    # =====================================================================
    # Channel map, pin numbers only.  "trips" always means the output SINKS,
    # pulling FAULT low, which is the only thing an open drain can do.
    # EVERY INPUT PIN IS ON A **PROTECTED** NODE (CMP_LED / CMP_BRD), never
    # on the raw divider - that is the E-2 fix and it is not optional:
    #
    #   OUT 1  IN- 6 = tap B (0.428 V), IN+ 7 = CMP_LED
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    #          -> sinks when CMP_LED > 3.055 V  = EMITTER OPEN / IMPLAUSIBLY
    #             COLD (-22.5/-3.8 C; a broken harness parks it near 3.30 V)
    #   OUT 13 IN- 10 = tap C (0.311 V), IN+ 11 = CMP_LED
    #          -> sinks when CMP_LED < 0.311 V  = EMITTER SHORT / RAIL-PINNED
    #             LOW (110.2/92.9 C equivalent; a real short parks it at 0 V)
    #   OUT 14 IN- 8  = tap C (0.311 V), IN+ 9  = CMP_BRD
    #          -> sinks when CMP_BRD < 0.311 V  = BOARD HOT (110.2/92.9 C)
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                     footprint=R0603)
    sh.wire_pins("R410", {"1": N_FAULT, "2": N_VREF_OPEN})

    # R412 + R414 IN SERIES = 200 k, FAULT -> CMP_BRD (IN+ pin 9).  Built
    # IDENTICALLY to the LED branch on purpose: tap C is shared by board-hot
    # and emitter-short, so the two branches must have the same gain for the
    # shared tap to mean the same temperature on both sensors.
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    # LEARNINGS 2026-07-28 - but Project.add_sheet honours it on the ROOT's
    # sheet pin, which is where it is read).
    #   FAULT    output : driven HERE (open drain, sinking only)
    #   NTC_LED  input  : arrives from `led_if` (J5 harness pin)
    #   ADC0/1   output : sourced HERE, on to `control` -> J4
    for i, (net, shape) in enumerate([
            (N_FAULT, "output"),
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
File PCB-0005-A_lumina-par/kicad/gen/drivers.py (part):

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    sets the sense threshold to 224/240/251 mV. THE 2.2 V IADJ REFERENCE
    DIVIDER WAS CONSIDERED AND REJECTED AT P3 (parts.json R301 role) - do
    not re-propose it.
  * pin 9 PWM doubles as ENABLE and as the VIN-UVLO comparator input. Here
    it is a static enable driven from `/DRV_ENn` (3.3 V CMOS through a 0 R
    link on the `control` sheet); the DIMMING is done by the shunt FET.
    **PWM abs max is 5.5 V - the pin is NOT 12 V tolerant** (p4-wiring-notes
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    SW, CSN, VCC = f"SW{n}", f"CSN{n}", f"VCC{n}"
    BOOT, COFF, SHG, SNUB = f"BOOT{n}", f"COFF{n}", f"SHG{n}", f"SNUB{n}"
    # hierarchical nets - NO leading slash here; the root's local label adds
    # it (lumina-carrier root.py: hier pin "CDB" -> final net "/CDB").
    LED_A, DRV_EN, SHUNT = f"LED{n}_A", f"DRV_EN{n}", f"SHUNT{n}"
    VCC_NET = f"/drivers/{VCC}"      # exact netlist name, for the metadata

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        ],
        caps_at=at(*CAPS_AT), caps_dx=CAPS_DX)

    # PWM (pin 9) = this channel's enable, from `control` (/EN_OK through a
    # 0 R link, or the DNP one-shot). 3.3 V CMOS against a 1.0 V typical
    # threshold and a 5.5 V ABS MAX. No capacitor, no RC: sec 8.3.11.2's
    # 0.1 uF applies to a static VIN-UVLO divider, and blocks.md B2 caps any
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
